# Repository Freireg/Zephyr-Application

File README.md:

# Zephyr-Application

## Overview
This is my personal Zephyr Workspace, in which I test and develop some basic interactions with Zephyr.

In this repository you may find some basic thread spawning examples, how to structure a project with an include folder, playing with overlay files, etc.

I'll be commenting on some of those examples in the future, so I can have some easy access examples.

## More usefull info
All the important stuff can be found in [Zephyr's Official Documentation](https://docs.zephyrproject.org/3.1.0/index.html).

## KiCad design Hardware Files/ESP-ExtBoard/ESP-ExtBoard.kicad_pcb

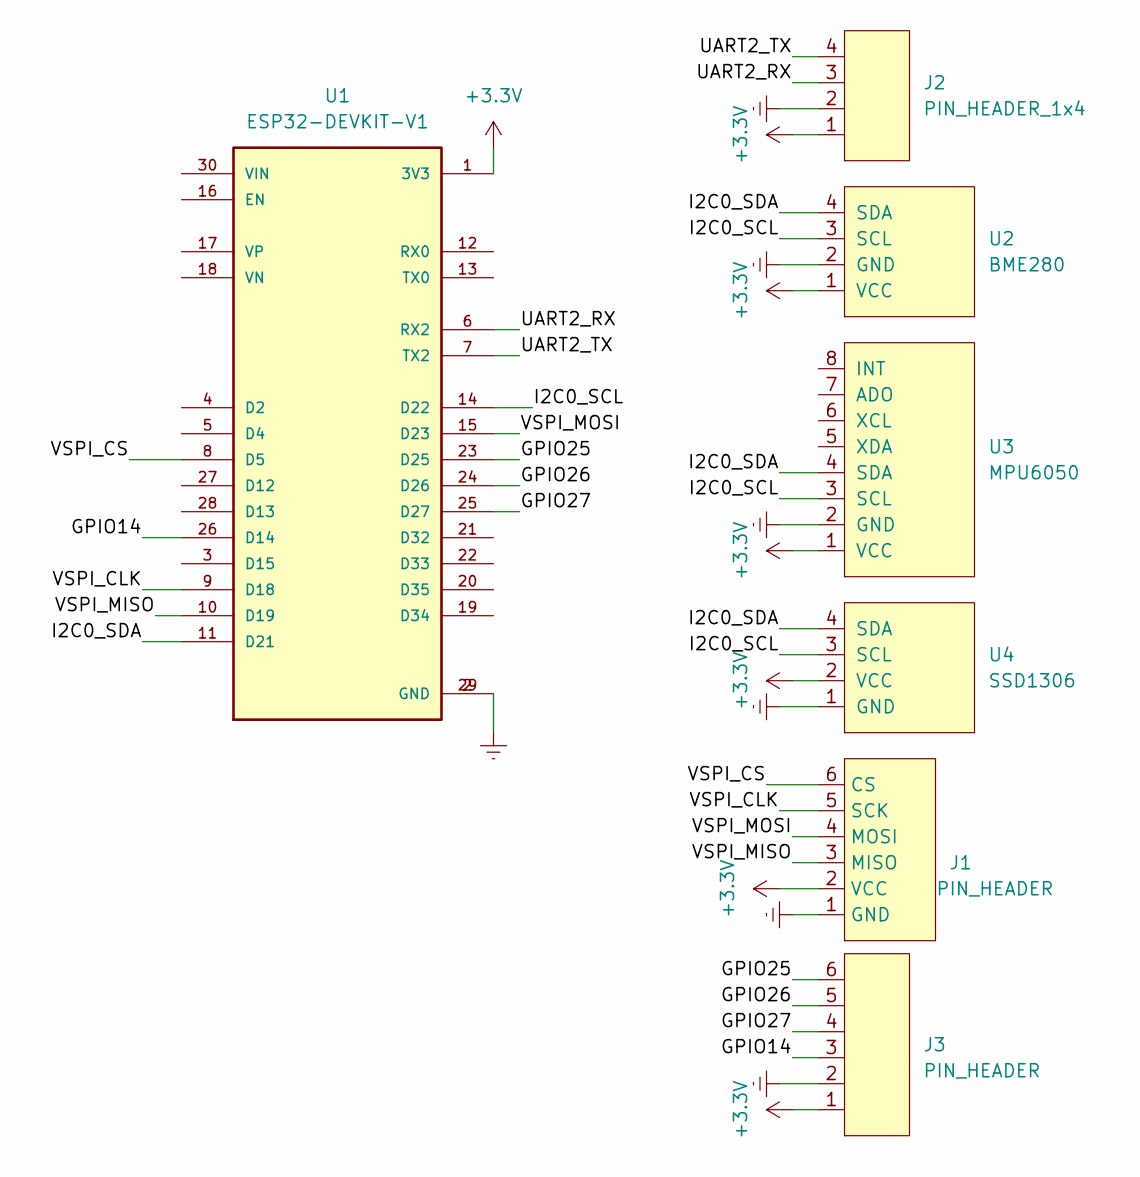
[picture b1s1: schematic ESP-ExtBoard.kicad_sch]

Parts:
J1: PIN_HEADER; PinHeader_1x06_P2.54mm_Vertical_1
J2: PIN_HEADER_1x4; PinHeader_1x04_P2.54mm_Vertical_1
J3: PIN_HEADER; PinHeader_1x06_P2.54mm_Vertical
U1: ESP32-DEVKIT-V1; MODULE_ESP32_DEVKIT_V1; PARTREV N/A
U2: BME280; PinHeader_1x04_P2.54mm_Vertical
U3: MPU6050; PinHeader_1x08_P2.54mm_Vertical
U4: SSD1306; 128x64OLED

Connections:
+3.3V: J1.2 (VCC), J2.1, J3.1, U1.1 (3V3), U2.1 (VCC), U3.1 (VCC), U4.2 (VCC)
+5V: U1.30 (VIN); also elsewhere on the board
/GPIO14: J3.3, U1.26 (D14)
/GPIO25: J3.6, U1.23 (D25)
/GPIO26: J3.5, U1.24 (D26)
/GPIO27: J3.4, U1.25 (D27)
/GPIO32: U1.21 (D32); also elsewhere on the board
/GPIO33: U1.22 (D33); also elsewhere on the board
/GPIO34: U1.19 (D34); also elsewhere on the board
/GPIO35: U1.20 (D35); also elsewhere on the board
/I2C0_SCL: U1.14 (D22), U2.3 (SCL), U3.3 (SCL), U4.3 (SCL)
/I2C0_SDA: U1.11 (D21), U2.4 (SDA), U3.4 (SDA), U4.4 (SDA)
/UART2_RX: J2.3, U1.6 (RX2)
/UART2_TX: J2.4, U1.7 (TX2)
/VSPI_CLK: J1.5 (SCK), U1.9 (D18)
/VSPI_CS: J1.6 (CS), U1.8 (D5)
/VSPI_MISO: J1.3 (MISO), U1.10 (D19)
/VSPI_MOSI: J1.4 (MOSI), U1.15 (D23)
Earth: J1.1 (GND), J2.2, J3.2, U1.2 (GND), U1.29 (GND), U2.2 (GND), U3.2 (GND), U4.1 (GND); also elsewhere on the board

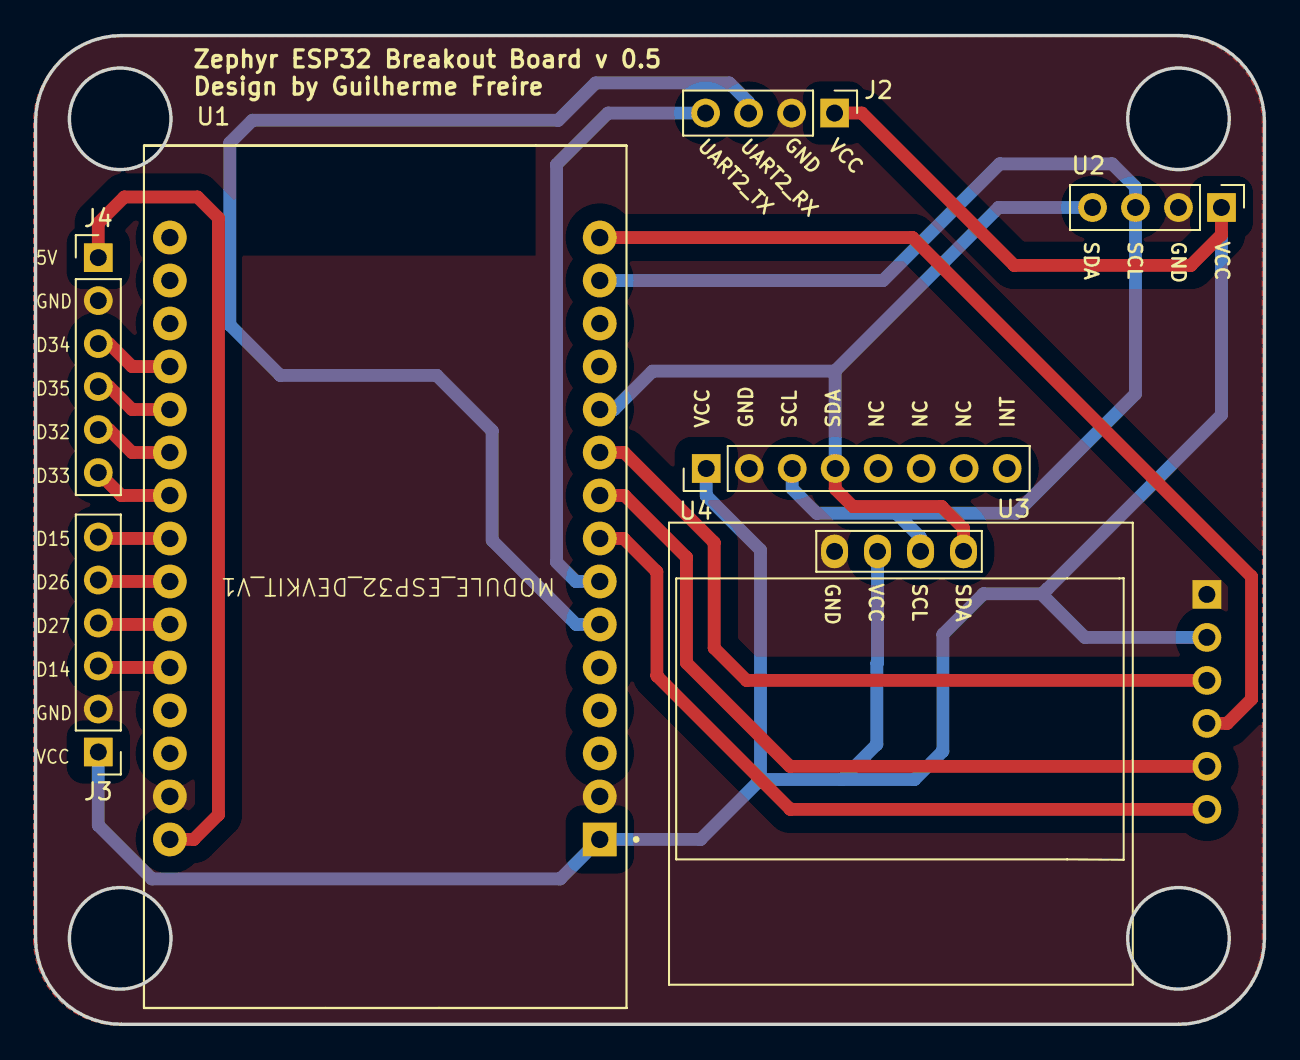
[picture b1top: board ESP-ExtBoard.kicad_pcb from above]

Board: 2 copper layers, 72.6 x 58.4 mm, 8 parts (1 on the bottom side), 19 nets.

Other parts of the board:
J4: PIN_HEADER; PinHeader_1x06_P2.54mm_Vertical

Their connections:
+5V: J4.1; also elsewhere on the board
/GPIO32: J4.5; also elsewhere on the board
/GPIO33: J4.6; also elsewhere on the board
/GPIO34: J4.3; also elsewhere on the board
/GPIO35: J4.4; also elsewhere on the board
Earth: J4.2; also elsewhere on the board

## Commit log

2022-08-23 My first commit
2022-08-24 Simple overlay implementation
2022-08-29 [Overlay] Adding MIPI-DSI
2022-10-08 [Doc] Updating README
2023-03-29 serial example
2023-04-16 cortex-debug not yet tested
2023-04-18 Second tutorial video
2023-04-18 Interrups tutorial
2023-04-21 Testing custom board
2023-04-26 Creating a OS Example
2023-04-27 Threads workin
2023-04-27 Spawning Threads in runing time, see the copy txt
2023-04-28 Threads spawning in main function
2023-05-04 Report task now prints the thread ID
2023-05-04 [New Example] How to include header files
2023-05-04 Readme Update
2023-05-08 Shell usage examples
2023-05-08 Minor quality of life shell changes
2023-05-08 Updating folder names
2023-05-08 [Doc] Creating some READMEs
2023-05-19 Sensor-example
2023-05-30 [New Example] Oled Display SSD1306
2023-05-31 [app update] Merging the OLED and Sensor examples
2023-06-05 [app-copy] working with threads
2023-06-09 [Hardware Files] Custom Breakout Board
2023-06-10 [Hardware] V0.1 finished
2023-06-10 [hardware] SD module pin update
2023-06-12 [hardware] minor updates
2023-06-14 [hardware] V1.0
2023-07-15 Imported BME280 example
2023-09-15 usb configuration for the rpi_pico
2023-10-31 Adding more examples
2023-10-31 Edge impulse example
